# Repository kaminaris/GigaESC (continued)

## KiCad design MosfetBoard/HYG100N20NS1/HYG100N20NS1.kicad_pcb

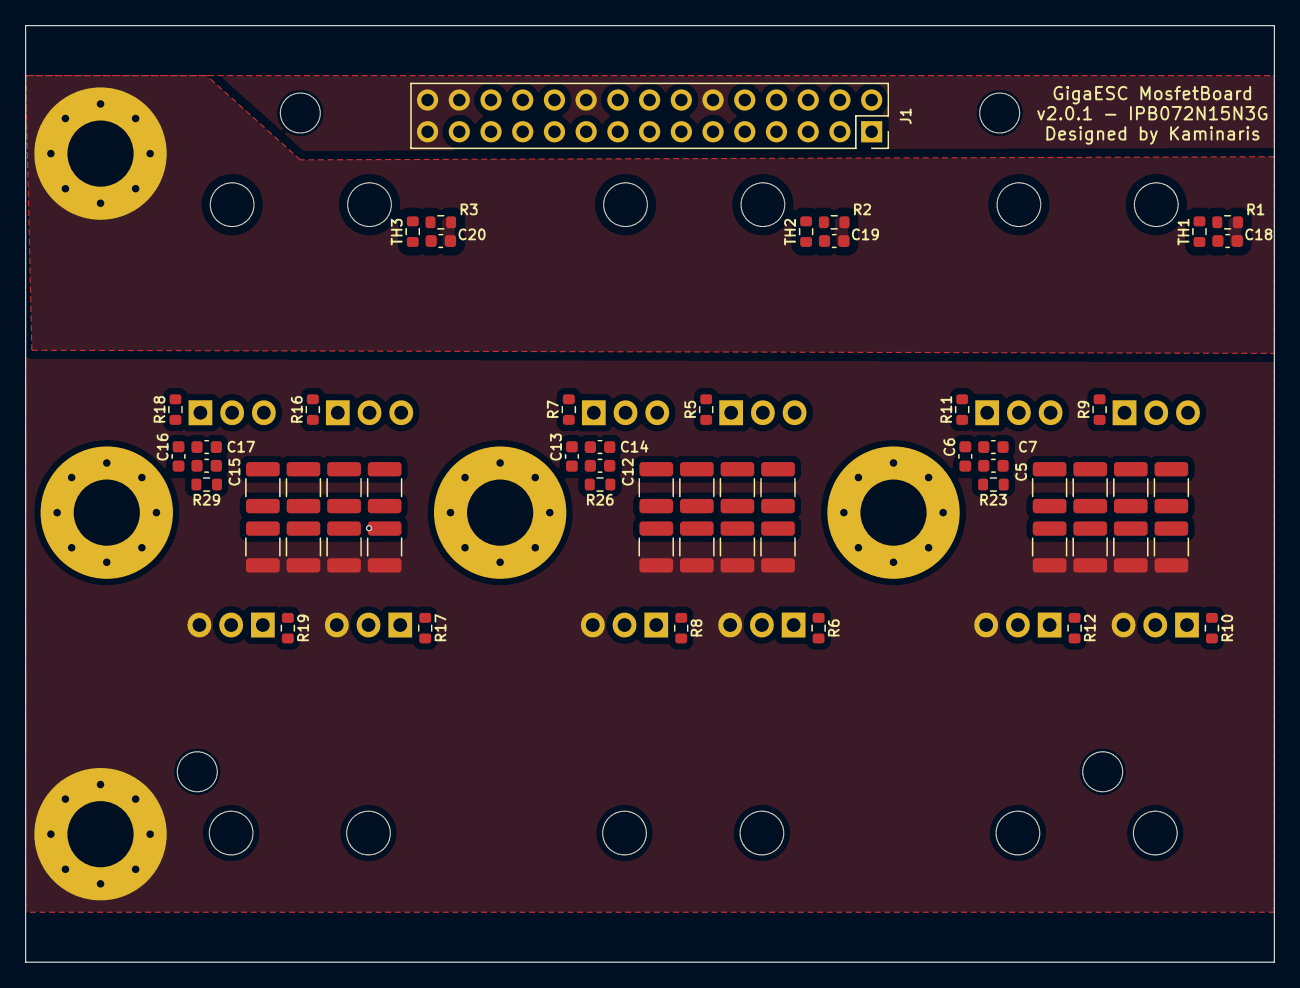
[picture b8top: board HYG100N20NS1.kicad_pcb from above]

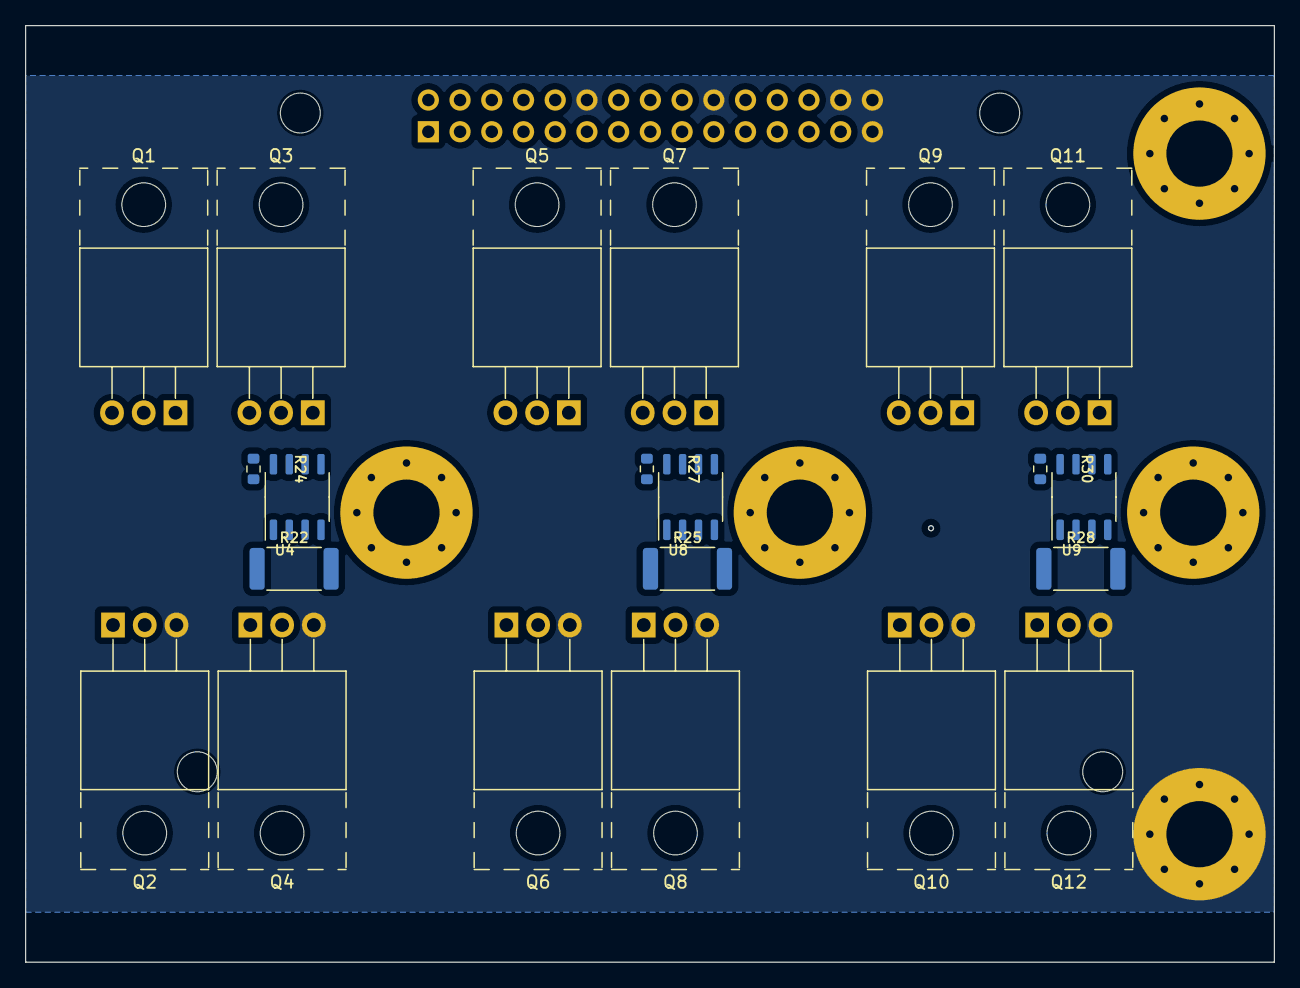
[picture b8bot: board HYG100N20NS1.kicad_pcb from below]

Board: 2 copper layers, 100.0 x 75.0 mm, 88 parts (21 on the bottom side), 55 nets, no tracks yet.

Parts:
C1, C2, C3, C4, C8, C9, C10, C11, C25, C26, C27, C28, C30, C31, C32, C33, C48, C49, C50, C51, C52, C53, C54, C55: 10u 100V; C_1210_3225Metric
C5, C12, C15: 100n; C_0603_1608Metric
C6, C13, C16: 10n; C_0603_1608Metric
C7, C14, C17: 1n; C_0603_1608Metric
C18, C19, C20: 1u; C_0603_1608Metric
H1, H2, H3, H4, H5: MountingHole_Pad; MountingHole_5.3mm_M5_Pad_Via
H6, H7, H8, H9: MountingHole; MountingHole_3.2mm_M3_ISO14580
J1: LogicConnector; PinSocket_2x15_P2.54mm_Vertical
Q1, Q2, Q3, Q4, Q5, Q6, Q7, Q8, Q9, Q10, Q11, Q12: HYG100N20NS1; TO-220-3_Horizontal_TabUp
R1, R2, R3: 10k; R_0603_1608Metric
R5, R6, R7, R8, R9, R10, R11, R12, R16, R17, R18, R19: 2.2; R_0603_1608Metric
R22, R25, R28: 0.3m; R_2512_6332Metric
R23, R26, R29: 4.7k; R_0603_1608Metric
R24, R27, R30: 9.1k; R_0603_1608Metric
TH1, TH2, TH3: NCP18XH103F03RB; R_0603_1608Metric
U4, U8, U9: MT9223CT-50BR5; SOP-8_3.9x4.9mm_P1.27mm

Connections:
+BATT: C1.1, C8.1, C10.1, C25.1, C26.1, C28.1, C31.1, C33.1, C48.1, C50.1, C52.1, C54.1, H5.1, Q1.2 (D), Q3.2 (D), Q5.2 (D), Q7.2 (D), Q9.2 (D), Q11.2 (D)
-BATT: C2.2, C3.2, C4.2, C9.2, C11.2, C18.2, C19.2, C20.2, C27.2, C30.2, C32.2, C49.2, C51.2, C53.2, C55.2, H4.1, J1.12, J1.20, J1.28, J1.29, J1.30, Q2.3 (S), Q4.3 (S), Q6.3 (S), Q8.3 (S), Q10.3 (S), Q12.3 (S), R1.2, R2.2, R3.2
/3.3V: J1.2, TH1.1, TH2.1, TH3.1
/5V: C5.2, C12.2, C15.2, J1.4, U4.8 (VCC), U8.8 (VCC), U9.8 (VCC)
/PH1: J1.6, R9.1, R11.1
/PH2: J1.14, R5.1, R7.1
/PH3: J1.22, R16.1, R18.1
/PHASE1: J1.8, Q1.3 (S), Q2.2 (D), Q3.3 (S), Q4.2 (D), R22.2, U4.1 (IP+), U4.2 (IP+)
/PHASE2: J1.16, Q5.3 (S), Q6.2 (D), Q7.3 (S), Q8.2 (D), R25.2, U8.1 (IP+), U8.2 (IP+)
/PHASE3: J1.24, Q9.3 (S), Q10.2 (D), Q11.3 (S), Q12.2 (D), R28.2, U9.1 (IP+), U9.2 (IP+)
/PL1: J1.10, R10.1, R12.1
/PL2: J1.18, R6.1, R8.1
/PL3: J1.26, R17.1, R19.1
/PhaseMosfets1/MOS_TEMP: C18.1, J1.5, R1.1, TH1.2
/PhaseMosfets1/PHASE_OUT: H1.1, R22.1, U4.3 (IP-), U4.4 (IP-)
/PhaseMosfets1/SH+: J1.11, R23.1, R24.2
/PhaseMosfets1/SH-: C5.1, C6.2, C7.2, J1.9, R24.1, U4.5 (GND)
/PhaseMosfets2/MOS_TEMP: C19.1, J1.13, R2.1, TH2.2
/PhaseMosfets2/PHASE_OUT: H2.1, R25.1, U8.3 (IP-), U8.4 (IP-)
/PhaseMosfets2/SH+: J1.19, R26.1, R27.2
/PhaseMosfets2/SH-: C12.1, C13.2, C14.2, J1.17, R27.1, U8.5 (GND)
/PhaseMosfets3/MOS_TEMP: C20.1, J1.21, R3.1, TH3.2
/PhaseMosfets3/PHASE_OUT: H3.1, R28.1, U9.3 (IP-), U9.4 (IP-)
/PhaseMosfets3/SH+: J1.27, R29.1, R30.2
/PhaseMosfets3/SH-: C15.1, C16.2, C17.2, J1.25, R30.1, U9.5 (GND)
unnamed: C1.2, C2.1
unnamed: C4.1, C48.2
unnamed: C8.2, C9.1
unnamed: C10.2, C11.1
unnamed: C3.1, C25.2
unnamed: C26.2, C27.1
unnamed: C28.2, C30.1
unnamed: C31.2, C32.1
unnamed: C33.2, C49.1
unnamed: C50.2, C51.1
unnamed: C52.2, C53.1
unnamed: C54.2, C55.1
unnamed: Q1.1 (G), R9.2
unnamed: Q2.1 (G), R10.2
unnamed: Q3.1 (G), R11.2
unnamed: Q4.1 (G), R12.2
unnamed: Q5.1 (G), R5.2
unnamed: Q6.1 (G), R6.2
unnamed: Q7.1 (G), R7.2
unnamed: Q8.1 (G), R8.2
unnamed: Q9.1 (G), R16.2
unnamed: Q10.1 (G), R17.2
unnamed: Q11.1 (G), R18.2
unnamed: Q12.1 (G), R19.2
unnamed: C6.1, U4.6 (FILTER)
unnamed: C7.1, R23.2, U4.7 (VIOUT)
unnamed: C13.1, U8.6 (FILTER)
unnamed: C14.1, R26.2, U8.7 (VIOUT)
unnamed: C16.1, U9.6 (FILTER)
unnamed: C17.1, R29.2, U9.7 (VIOUT)

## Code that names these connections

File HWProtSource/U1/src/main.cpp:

/*
  created  27 Jun 2023
  by Euan Mutch (TechAUmNu)
*/

#include <Arduino.h>
#include <Comparator.h>
#include <Event.h>
#include <Logic.h>
#include <Wire.h>

#define wdtReset() __asm__ __volatile__ ("wdr"::)

#define IS_TEST_MODE
#define IS_HIGH_SIDE
#define HAS_I2C

#define POT_A_ADDRESS 0x2E    // 0b0101110
#define POT_B_ADDRESS 0x3E    // 0b0111110

#define POT_ADDRESS POT_B_ADDRESS

#define LOW_SIDE_SETTING (127 - 5)
#define HIGH_SIDE_SETTING 5

#define POT_SETTING LOW_SIDE_SETTING

void setPotValue(uint8_t addr, uint8_t value) {
	wdtReset();
	delay(100);
	Wire.beginTransmission(addr);
	Wire.write(0x00);         // sends instruction.  0x00 = Write
	Wire.write(value);         // sends value 0 = 10K, 127 = 0K
	auto res = Wire.endTransmission();     // end transmission
	Serial.printf("i2c res: %d\n", res);
	delay(100);
	wdtReset();
}

void setup() {
	// disabled
	#ifdef IS_TEST_MODE
	pinMode(PIN_PA4, OUTPUT);
	digitalWrite(PIN_PA4, LOW);
	#else
	_PROTECTED_WRITE(WDT.CTRLA, WDT_PERIOD_1KCLK_gc);

	Serial.begin(115200);
	while (!Serial) {
		wdtReset();
		delay(1);
	}
	Serial.printf("Started at %d MHz\n", F_CPU);

	// Configure event channel for reset from GPIO pin PB2
	Event1.set_generator(0xFF);
	Event1.set_user(user::ccl1_event_a);
	Event1.start();

	// Initialize logic block 1
	Logic1.enable = true;                 // Enable logic block 1
	Logic1.input0 = logic::in::event_a;     // Connect input 0 to ccl1_event_a (PB2 through Event1)
	Logic1.input1 = logic::in::masked;
	Logic1.input2 = logic::in::masked;
	Logic1.output = logic::out::disable;
	Logic1.truth = 0xFE;  // Set truth table
	Logic1.init();

	// Configure relevant comparator parameters
	Comparator0.input_p = comparator::in_p::in2;  // Use positive input 2 (PB1)
	Comparator1.input_p = comparator::in_p::in3;  // Use positive input 3 (PB4)
	Comparator2.input_p = comparator::in_p::in1;  // Use positive input 1 (PB0)

	// Initialize comparators
	Comparator0.init();
	Comparator1.init();
	Comparator2.init();

	// Configure logic block
	Logic0.enable = true;
	Logic0.input0 = logic::in::ac0;
	Logic0.input1 = logic::in::ac1;
	Logic0.input2 = logic::in::ac2;
	Logic0.output = logic::out::enable;
	Logic0.filter = logic::filter::filter;
	Logic0.sequencer = logic::sequencer::rs_latch;    // Latch output
	Logic0.truth = 0xFE;                            // Set truth table (3 input OR)
	Logic0.init();

	// Start comparators
	Comparator0.start();
	Comparator1.start();
	Comparator2.start();

	// Start the AVR logic hardware
	Logic::start();

		#ifdef HAS_I2C
	Wire.swap(1);
	Wire.begin();
	// A is connected to HIGH side, B to LOW side

	setPotValue(POT_ADDRESS, POT_SETTING);

		#endif
	analogReference(EXTERNAL); // PA5
	analogClockSpeed(-1);
	#endif
}

void loop() {
	wdtReset();

	delay(500);
	Serial.println("ping");
}

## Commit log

2023-06-23 ignore
2023-06-23 initial
2023-06-24 drivers
2023-06-26 jlcpcb
2023-06-26 routinglogic
2023-06-27 routed
2023-06-27 driversconnectors
2023-06-28 driversboard
2023-06-29 routed_again
2023-06-29 pre-final
2023-06-29 schup
2023-06-29 renamed
2023-06-29 fixes, led R
2023-06-30 nearfinish
2023-06-30 or-gate
2023-06-30 project_rename
2023-07-01 UCC21520DWR
2023-07-01 NSi6602B-DSWR
2023-07-02 organization
2023-07-04 new_format
2023-07-04 rename
2023-07-05 cheap_board
2023-07-06 cheap-mosfet-board
2023-07-10 shunts
2023-07-11 ltc7801
2023-07-12 nearlyready
2023-07-15 removed trash
2023-07-15 fixed ignore
2023-07-15 cleanup
2023-07-17 initialv2
2023-07-19 small fixes
2023-07-20 wholeDevice
2023-07-20 fixing_giga_mistake
2023-07-21 fixeddimensions
2023-07-23 movedconnectors
2023-07-24 moved libs and gigamax version
2023-07-30 small changes for lt
2023-07-30 ucc fixes
2023-08-04 minor
2023-08-06 fixes to caps
2023-08-06 fixes to caps and resistors on UCC21520DWR
2023-08-07 v2.3
2023-08-08 v2.4 - INA4181A1IPWR
2023-08-08 v2.5 - routed
2023-08-09 small changes
2023-08-09 dummy
2023-08-11 v2.6.0
2023-08-11 v2.6.0 - cleanup
2023-08-12 v2.6.1 - EPC2304
2023-08-12 v2.6.2 - EPC2304
2023-08-13 v2.7.0 - Phase shunts
2023-08-14 v2.8.0 - Small Hall sensors
2023-08-15 v2.9.0 - Small Hall/low side shunt
2023-08-15 v2.10.0 - Low side shunt and hall sensor
2023-08-15 v2.10.0 - Low side shunt and hall sensor - logic routed
2023-08-15 v2.10.0 - Low side shunt and hall sensor - current filters
2023-08-16 v2.10.0 - Low side shunt and hall sensor - epc routed
2023-08-16 v2.10.0 - Low side shunt and hall sensor - epc finished
2023-08-16 v2.10.0 - Release
2023-09-11 v2.10.1 - GaN Working
2023-09-15 v3.0.0 - GaN redesign begin
2023-11-25 v3.0.1 - GaN redesign
2023-11-25 v3.0.1 - Readme fix
2023-11-25 v3.0.1 - Devkit rerouted
2023-11-26 v3.0.2 - IPB v2
2023-11-29 v3.0.2 - Prerelease
2024-01-21 v3.0.3 - Cosmetic Changes
2024-02-22 v3.0.4 - EPC resistor changes
2024-02-22 v3.0.5 - Licence update
2024-02-28 v3.1.0 - Power supply fixes
2024-02-28 v3.1.1 - TO220 mosfets
2024-03-11 v3.2.0 - Moving to kicad 8
2024-03-11 v3.2.0 - Changelog
2024-03-26 v3.2.2 - TL494V2
2024-04-20 v3.3.0 - TL494V2
2024-04-26 v3.3.1 - Supervisor routed
2024-05-03 pio ini
2024-05-03 ignore fix
2024-05-07 Supervisor FW
2024-05-23 EPC board update
2024-05-29 v3.3.2 - ECP2304 changes
2024-05-29 v3.3.2 - gitignore
2024-05-29 v3.3.2 - EPC readme updated and schematic revised
2024-06-21 v3.3.3 - EPC pcb revised
2025-08-27 doc updates
